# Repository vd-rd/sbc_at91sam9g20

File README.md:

# Microchip AT91SAM9G20

## Description
 The follow-up to my previous [SBC based on AT91SAM9260](https://github.com/vd-rd/sbc_at91sam9260), enhancing the board specs in computing power and flexibility. The board is smaller 60x40mm now (SAM9260 was 80x40mm) while keeping the same amount of supported RAM and interfaces. AT91SAM9G20 boosts core speed to 400MHz and bus speed to 133MHz.
 
Board overview (draft):
[TBD]

### Features

| Characteristic | Description |
| --- | --- |
| Dimensions | 60mm x 40mm |
| Processor | AT91SAM9G20 - ARM926EJ @ 400MHz |
| Oscillators |  18.432MHz main clock, 32.768kHz RTC |
| RAM | SDRAM 128MB max (2x512Mbit modules) |
| Storage | microSD |
| USB | 1 microUSB client, 2 USB Host|
| Ethernet | RMII header |
| WiFi/BT | N/A |
| Supply | USB 5V, ACIN 5V |

Common interfaces such as I2C, SPI, UART and GPIO are exposed on the header.

### Building and flashing

Build U-Boot and Linux kernel + rootFS - TBD

Flash to SDCard - TBD

### Resources

You can find all necesary information to build or evaluate the module here:
   - [Fabrication files](https://github.com/vd-rd/sbc_alw_a13/releases)

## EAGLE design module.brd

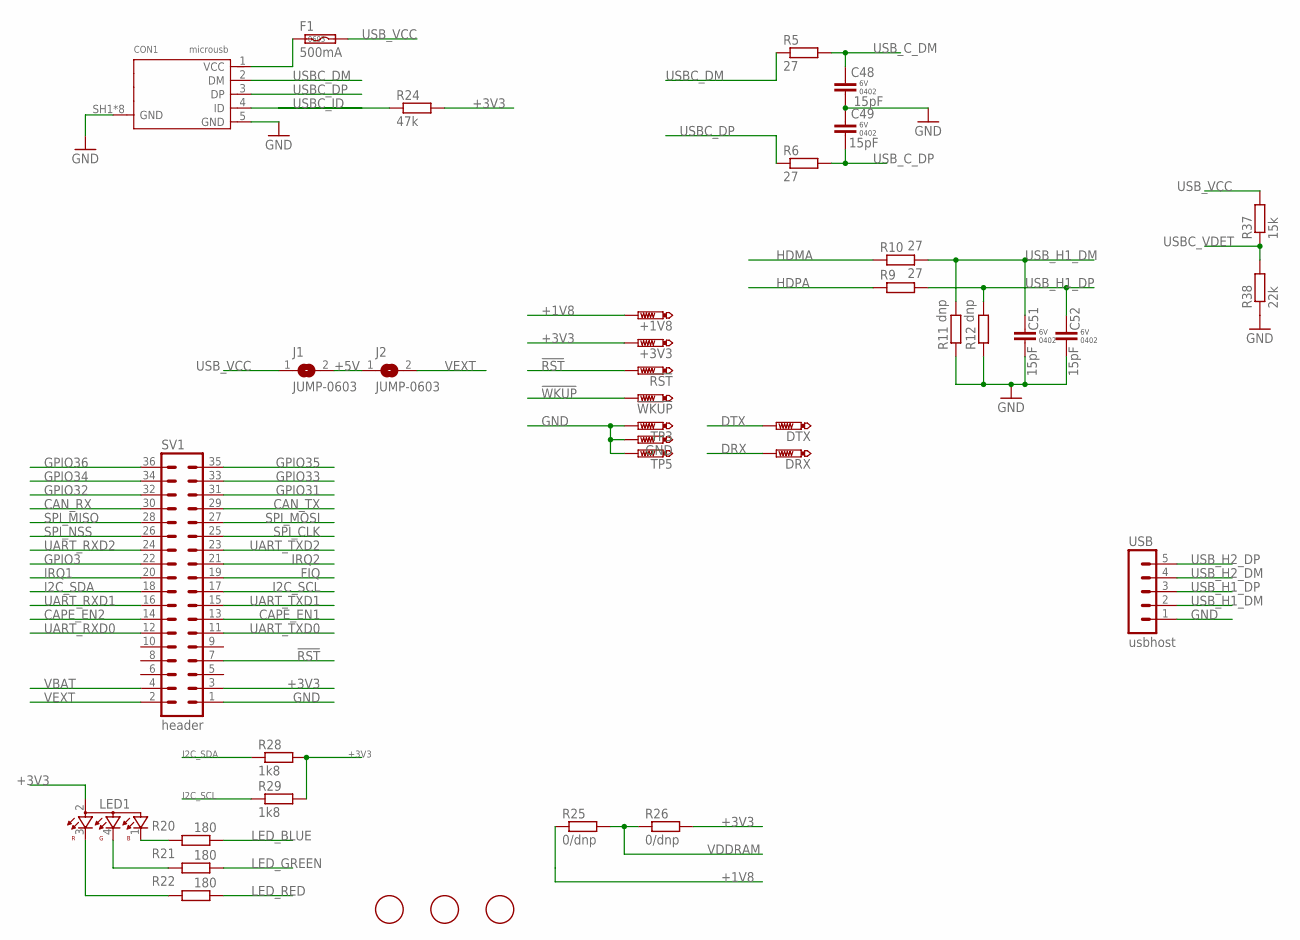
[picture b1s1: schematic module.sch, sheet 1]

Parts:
!RST: PTR1B1,27; B1,27
!WKUP: PTR1B1,27; B1,27
+1V8, +3V3: PTR1B1,27; B1,27
C48, C49, C51, C52: 15pF; C0402K
CON1: microusb; 10118194
DRX: PTR1B1,27; B1,27
DTX: PTR1B1,27; B1,27
F1: 500mA; F0603
GND: PTR1B1,27; B1,27
J1, J2: JUMP-0603; C0603
LED1: OSTB1204C1E; 321015RGB
R5, R6, R9, R10: 27; R0402
R11, R12: dnp; R0402
R20, R21, R22: 180; R0402
R24: 47k; R0402
R25, R26: 0/dnp; R0603
R28, R29: 1k8; R0402
R37: 15k; R0402
R38: 22k; R0402
SV1: header; MA18-2
TP3, TP5: PTR1B1,27; B1,27
U$1, U$2, U$3: FIDUCIAL; FIDUCIAL_1MM
USB: usbhost; MA05-1

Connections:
!RST: !RST.TP, SV1.7; also elsewhere on the board
!WKUP: !WKUP.TP; also elsewhere on the board
+1V8: +1V8.TP, R25.1; also elsewhere on the board
+3V3: +3V3.TP, LED1.2, R24.2, R26.2, R28.2, R29.2, SV1.3; also elsewhere on the board
+5V: J1.2, J2.1
CAN_RX: SV1.30
CAN_TX: SV1.29
CAPE_EN1: SV1.13; also elsewhere on the board
CAPE_EN2: SV1.14; also elsewhere on the board
DRX: DRX.TP; also elsewhere on the board
DTX: DTX.TP; also elsewhere on the board
FIQ: SV1.19; also elsewhere on the board
GND: C48.2, C49.2, C51.2, C52.2, CON1.5 (GND), CON1.SH1 (GND), CON1.SH2 (GND), CON1.SH3 (GND), CON1.SH4 (GND), CON1.SH5 (GND), CON1.SH6 (GND), CON1.SH7 (GND), CON1.SH8 (GND), GND.TP, R11.1, R12.1, R38.1, SV1.1, TP3.TP, TP5.TP, USB.1; also elsewhere on the board
GPIO3: SV1.22; also elsewhere on the board
GPIO31: SV1.31; also elsewhere on the board
GPIO32: SV1.32; also elsewhere on the board
GPIO33: SV1.33; also elsewhere on the board
GPIO34: SV1.34; also elsewhere on the board
GPIO35: SV1.35; also elsewhere on the board
GPIO36: SV1.36; also elsewhere on the board
HDMA: R10.1; also elsewhere on the board
HDPA: R9.1; also elsewhere on the board
I2C_SCL: R29.1, SV1.17; also elsewhere on the board
I2C_SDA: R28.1, SV1.18; also elsewhere on the board
IRQ1: SV1.20; also elsewhere on the board
IRQ2: SV1.21; also elsewhere on the board
LED_BLUE: R20.1; also elsewhere on the board
LED_GREEN: R21.1; also elsewhere on the board
LED_RED: R22.1; also elsewhere on the board
unnamed: CON1.1 (VCC), F1.1
unnamed: LED1.1, R20.2
unnamed: LED1.4, R21.2
unnamed: LED1.3, R22.2
SPI_CLK: SV1.25; also elsewhere on the board
SPI_MISO: SV1.28; also elsewhere on the board
SPI_MOSI: SV1.27; also elsewhere on the board
SPI_NSS: SV1.26; also elsewhere on the board
UART_RXD0: SV1.12; also elsewhere on the board
UART_RXD1: SV1.16; also elsewhere on the board
UART_RXD2: SV1.24; also elsewhere on the board
UART_TXD0: SV1.11; also elsewhere on the board
UART_TXD1: SV1.15; also elsewhere on the board
UART_TXD2: SV1.23; also elsewhere on the board
USBC_DM: CON1.2 (DM), R5.1
USBC_DP: CON1.3 (DP), R6.1
USBC_ID: CON1.4 (ID), R24.1; also elsewhere on the board
USBC_VDET: R37.1, R38.2; also elsewhere on the board
USB_C_DM: C48.1, R5.2; also elsewhere on the board
USB_C_DP: C49.1, R6.2; also elsewhere on the board
USB_H1_DM: C51.1, R10.2, R11.2, USB.2
USB_H1_DP: C52.1, R9.2, R12.2, USB.3
USB_H2_DM: USB.4
USB_H2_DP: USB.5
USB_VCC: F1.2, J1.1, R37.2
VBAT: SV1.4
VDDRAM: R25.2, R26.1; also elsewhere on the board
VEXT: J2.2, SV1.2

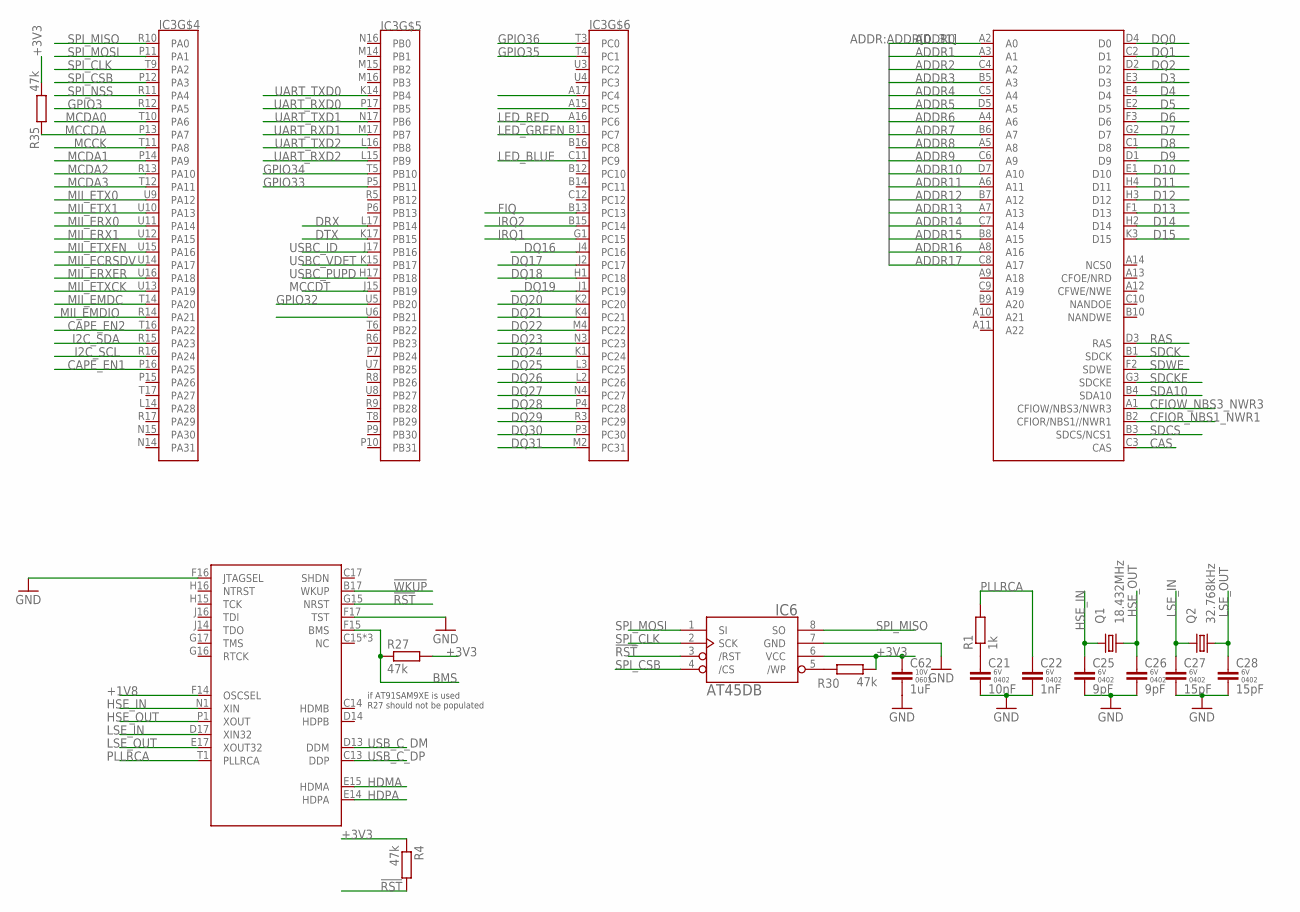
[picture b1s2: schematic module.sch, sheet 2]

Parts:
C21: 10nF; C0402K
C22: 1nF; C0402K
C25, C26: 9pF; C0402K
C27, C28: 15pF; C0402K
C62: 1uF; C0603
IC3: AT91SAM9260-BGA; BGA217C80P17X17_1500X1500X100
IC6: AT45DB-S; SO08-208
Q1: 18.432MHz; 3215
Q2: 32.768kHz; 3215
R1: 1k; R0402
R4, R27, R30, R35: 47k; R0402

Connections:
!RST: IC3.G15 (NRST), IC6.3 (/RST), R4.2; also elsewhere on the board
!WKUP: IC3.B17 (WKUP); also elsewhere on the board
+1V8: IC3.F14 (OSCSEL); also elsewhere on the board
+3V3: C62.1, IC6.6 (VCC), R4.1, R27.2, R30.2, R35.2; also elsewhere on the board
ADDR0: IC3.A2 (A0)
ADDR1: IC3.A3 (A1)
ADDR2: IC3.C4 (A2)
ADDR3: IC3.B5 (A3)
ADDR4: IC3.C5 (A4)
ADDR5: IC3.D5 (A5)
ADDR6: IC3.A4 (A6)
ADDR7: IC3.B6 (A7)
ADDR8: IC3.A5 (A8)
ADDR9: IC3.C6 (A9)
ADDR10: IC3.D7 (A10)
ADDR11: IC3.A6 (A11)
ADDR12: IC3.B7 (A12)
ADDR13: IC3.A7 (A13)
ADDR14: IC3.C7 (A14)
ADDR15: IC3.B8 (A15)
ADDR16: IC3.A8 (A16)
ADDR17: IC3.C8 (A17)
BMS: IC3.F15 (BMS), R27.1
CAPE_EN1: IC3.P16 (PA25); also elsewhere on the board
CAPE_EN2: IC3.T16 (PA22); also elsewhere on the board
CAS: IC3.C3 (CAS); also elsewhere on the board
CFIOR_NBS1_NWR1: IC3.B2 (CFIOR/NBS1//NWR1); also elsewhere on the board
CFIOW_NBS3_NWR3: IC3.A1 (CFIOW/NBS3/NWR3); also elsewhere on the board
D3: IC3.E3 (D3); also elsewhere on the board
D4: IC3.E4 (D4); also elsewhere on the board
D5: IC3.E2 (D5); also elsewhere on the board
D6: IC3.F3 (D6); also elsewhere on the board
D7: IC3.G2 (D7); also elsewhere on the board
D8: IC3.C1 (D8); also elsewhere on the board
D9: IC3.D1 (D9); also elsewhere on the board
D10: IC3.E1 (D10); also elsewhere on the board
D11: IC3.H4 (D11); also elsewhere on the board
D12: IC3.H3 (D12); also elsewhere on the board
D13: IC3.F1 (D13); also elsewhere on the board
D14: IC3.H2 (D14); also elsewhere on the board
D15: IC3.K3 (D15); also elsewhere on the board
DQ0: IC3.D4 (D0); also elsewhere on the board
DQ1: IC3.C2 (D1); also elsewhere on the board
DQ2: IC3.D2; also elsewhere on the board
DQ16: IC3.J4 (PC16); also elsewhere on the board
DQ17: IC3.J2 (PC17); also elsewhere on the board
DQ18: IC3.H1 (PC18); also elsewhere on the board
DQ19: IC3.J1 (PC19); also elsewhere on the board
DQ20: IC3.K2 (PC20); also elsewhere on the board
DQ21: IC3.K4 (PC21); also elsewhere on the board
DQ22: IC3.M4 (PC22); also elsewhere on the board
DQ23: IC3.N3 (PC23); also elsewhere on the board
DQ24: IC3.K1 (PC24); also elsewhere on the board
DQ25: IC3.L3 (PC25); also elsewhere on the board
DQ26: IC3.L2 (PC26); also elsewhere on the board
DQ27: IC3.N4 (PC27); also elsewhere on the board
DQ28: IC3.P4 (PC28); also elsewhere on the board
DQ29: IC3.R3 (PC29); also elsewhere on the board
DQ30: IC3.P3 (PC30); also elsewhere on the board
DQ31: IC3.M2 (PC31); also elsewhere on the board
DRX: IC3.L17 (PB14); also elsewhere on the board
DTX: IC3.K17 (PB15); also elsewhere on the board
FIQ: IC3.B13 (PC13); also elsewhere on the board
GND: C21.2, C22.2, C25.2, C26.2, C27.2, C28.2, C62.2, IC3.F17 (TST), IC6.7 (GND); also elsewhere on the board
GPIO3: IC3.R12 (PA5); also elsewhere on the board
GPIO31: IC3.U6 (PB21); also elsewhere on the board
GPIO32: IC3.U5 (PB20); also elsewhere on the board
GPIO33: IC3.P5 (PB11); also elsewhere on the board
GPIO34: IC3.T5 (PB10); also elsewhere on the board
GPIO35: IC3.T4 (PC1); also elsewhere on the board
GPIO36: IC3.T3 (PC0); also elsewhere on the board
HDMA: IC3.E15 (HDMA); also elsewhere on the board
HDPA: IC3.E14 (HDPA); also elsewhere on the board
HSE_IN: C25.1, IC3.N1 (XIN), Q1.1
HSE_OUT: C26.1, IC3.P1 (XOUT), Q1.3 (2)
I2C_SCL: IC3.R16 (PA24); also elsewhere on the board
I2C_SDA: IC3.R15 (PA23); also elsewhere on the board
IRQ1: IC3.G1 (PC15); also elsewhere on the board
IRQ2: IC3.B15 (PC14); also elsewhere on the board
LED_BLUE: IC3.C11 (PC9); also elsewhere on the board
LED_GREEN: IC3.B11 (PC7); also elsewhere on the board
LED_RED: IC3.A16 (PC6); also elsewhere on the board
LSE_IN: C27.1, IC3.D17 (XIN32), Q2.1
LSE_OUT: C28.1, IC3.E17 (XOUT32), Q2.2
MCCDA: IC3.P13 (PA7), R35.1; also elsewhere on the board
MCCDT: IC3.J15 (PB19); also elsewhere on the board
MCCK: IC3.T11 (PA8); also elsewhere on the board
MCDA0: IC3.T10 (PA6); also elsewhere on the board
MCDA1: IC3.P14 (PA9); also elsewhere on the board
MCDA2: IC3.R13 (PA10); also elsewhere on the board
MCDA3: IC3.T12 (PA11); also elsewhere on the board
MII_ECRSDV: IC3.U14 (PA17); also elsewhere on the board
MII_EMDC: IC3.T14 (PA20); also elsewhere on the board
MII_EMDIO: IC3.R14 (PA21); also elsewhere on the board
MII_ERX0: IC3.U11 (PA14); also elsewhere on the board
MII_ERX1: IC3.U12 (PA15); also elsewhere on the board
MII_ERXER: IC3.U16 (PA18); also elsewhere on the board
MII_ETX0: IC3.U9 (PA12); also elsewhere on the board
MII_ETX1: IC3.U10 (PA13); also elsewhere on the board
MII_ETXCK: IC3.U13 (PA19); also elsewhere on the board
MII_ETXEN: IC3.U15 (PA16); also elsewhere on the board
unnamed: C21.1, R1.1
unnamed: IC6.5 (/WP), R30.1
PLLRCA: C22.1, IC3.T1 (PLLRCA), R1.2
RAS: IC3.D3 (RAS); also elsewhere on the board
SDA10: IC3.B4 (SDA10); also elsewhere on the board
SDCK: IC3.B1 (SDCK); also elsewhere on the board
SDCKE: IC3.G3 (SDCKE); also elsewhere on the board
SDCS: IC3.B3 (SDCS/NCS1); also elsewhere on the board
SDWE: IC3.F2 (SDWE); also elsewhere on the board
SPI_CLK: IC3.T9 (PA2), IC6.2 (SCK); also elsewhere on the board
SPI_CSB: IC3.P12 (PA3), IC6.4 (/CS)
SPI_MISO: IC3.R10 (PA0), IC6.8 (SO); also elsewhere on the board
SPI_MOSI: IC3.P11 (PA1), IC6.1 (SI); also elsewhere on the board
SPI_NSS: IC3.R11 (PA4); also elsewhere on the board
UART_RXD0: IC3.P17 (PB5); also elsewhere on the board
UART_RXD1: IC3.M17 (PB7); also elsewhere on the board
UART_RXD2: IC3.L15 (PB9); also elsewhere on the board
UART_TXD0: IC3.K14 (PB4); also elsewhere on the board
UART_TXD1: IC3.N17 (PB6); also elsewhere on the board
UART_TXD2: IC3.L16 (PB8); also elsewhere on the board
USBC_ID: IC3.J17 (PB16); also elsewhere on the board
USBC_PUPD: IC3.H17 (PB18)
USBC_VDET: IC3.K15 (PB17); also elsewhere on the board
USB_C_DM: IC3.D13 (DDM); also elsewhere on the board
USB_C_DP: IC3.C13 (DDP); also elsewhere on the board

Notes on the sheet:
if AT91SAM9XE is used R27 should not be populated

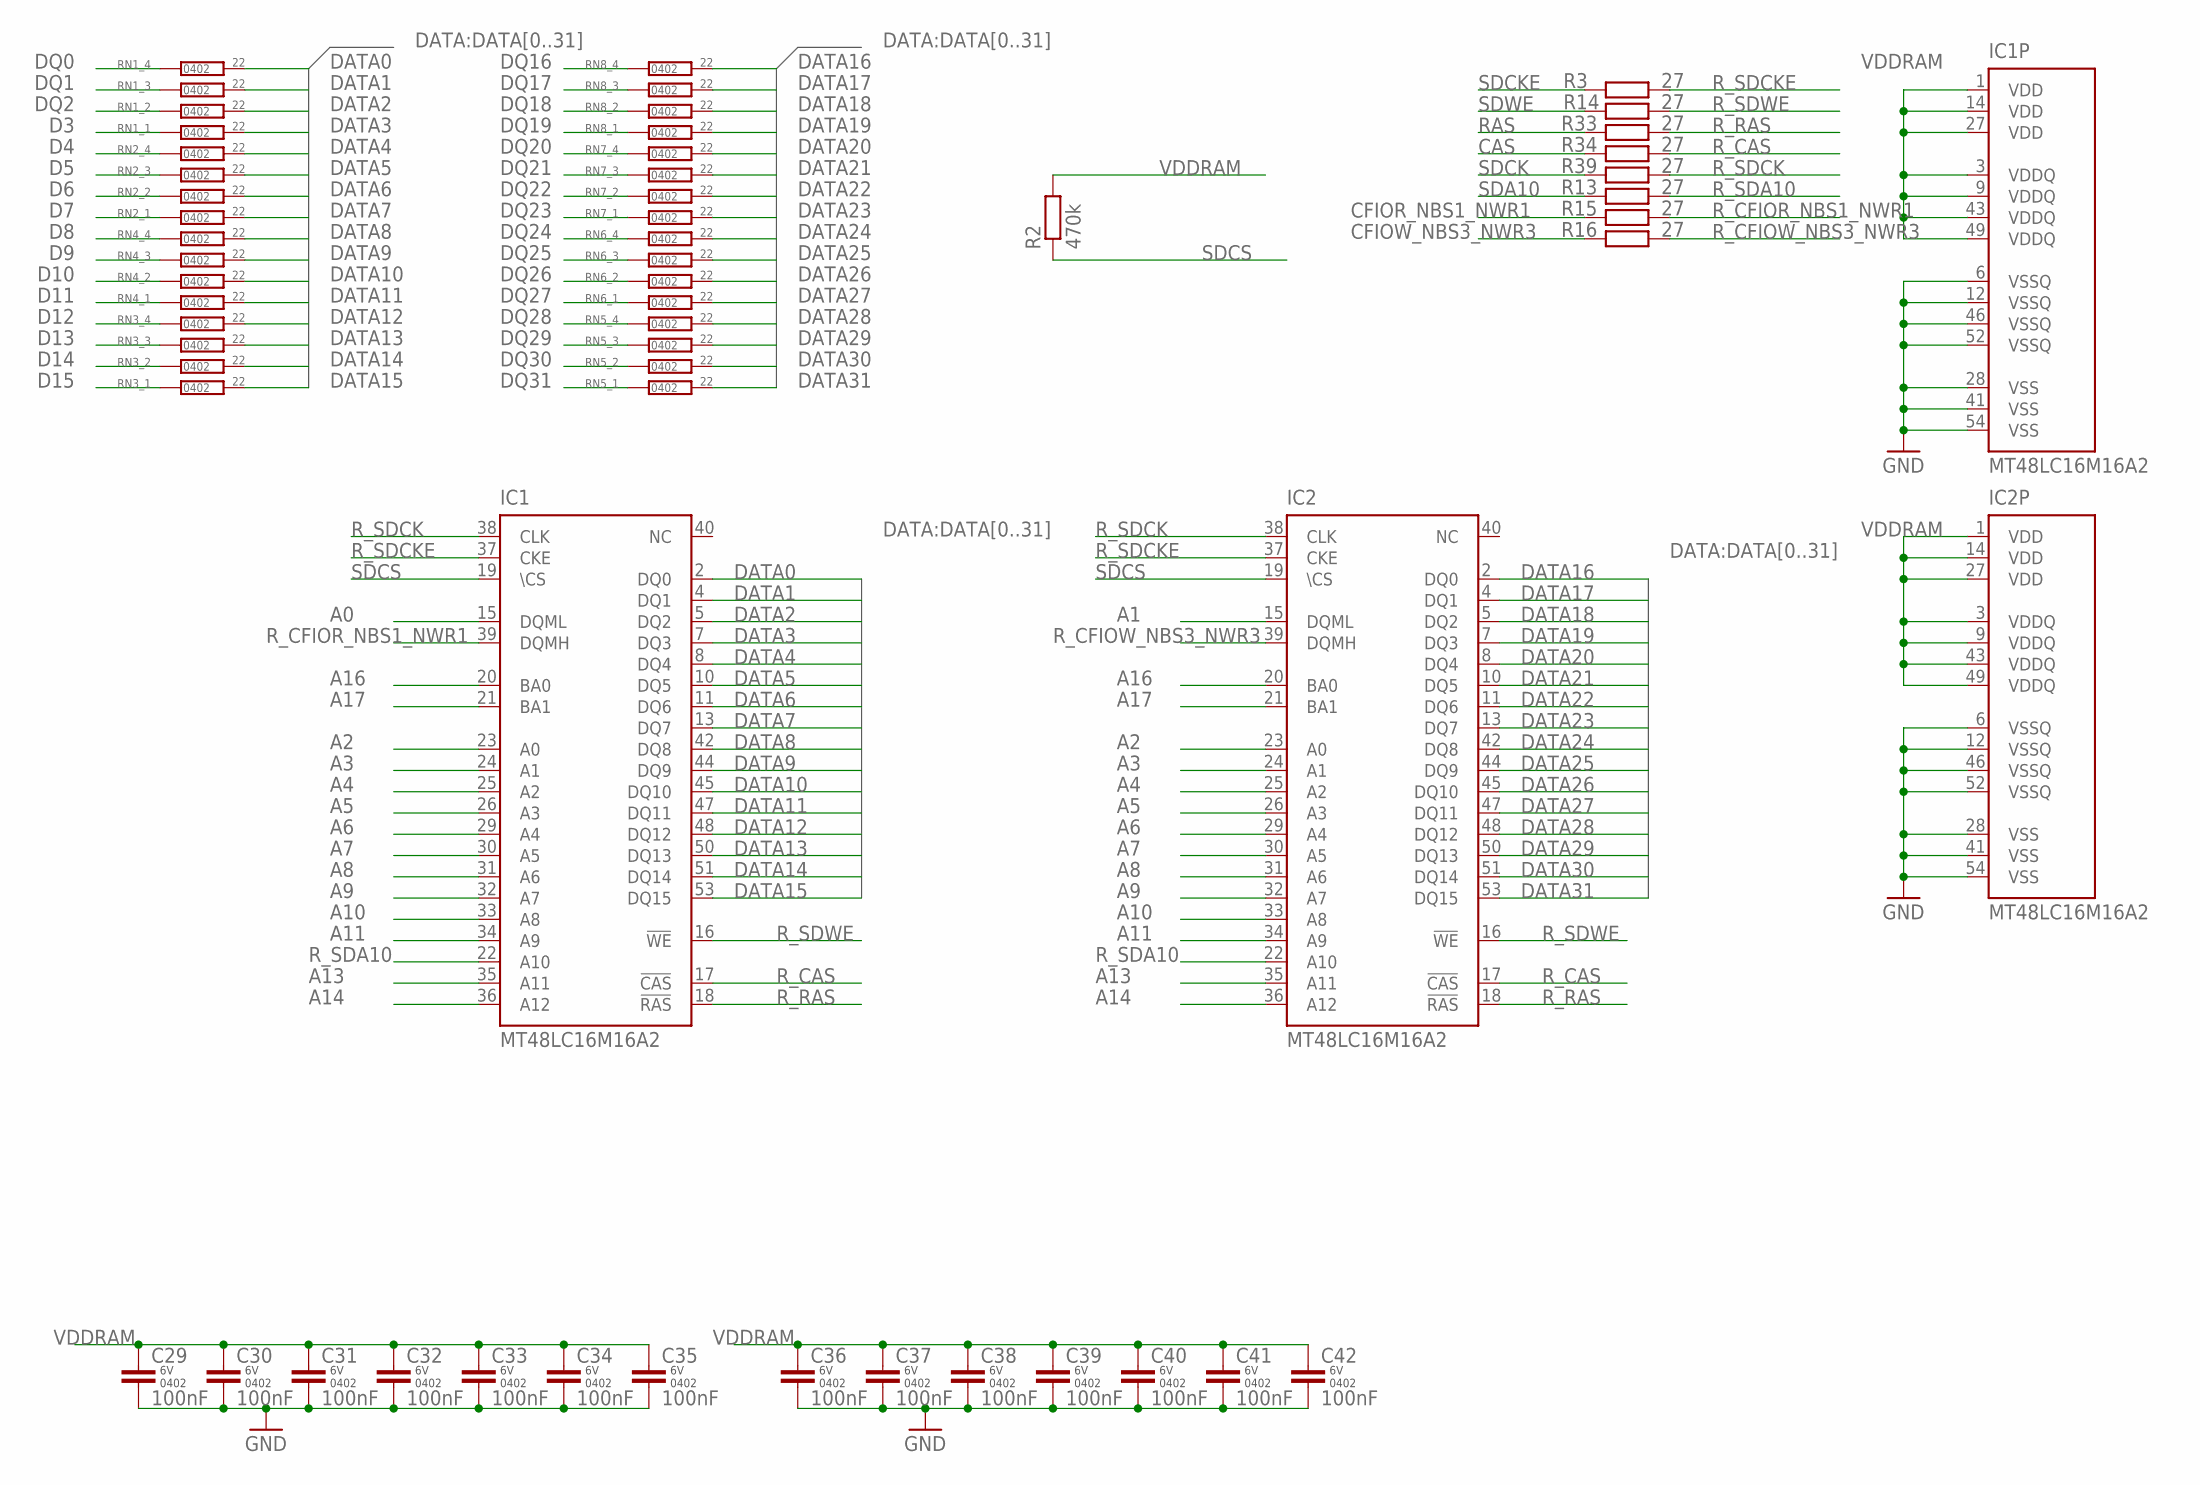
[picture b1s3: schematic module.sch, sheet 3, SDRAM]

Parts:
C29, C30, C31, C32, C33, C34, C35, C36, C37, C38, C39, C40, C41, C42: 100nF; C0402K
IC1, IC2: MT48LC16M16A2; TSOP54-400
R2: 470k; R0402
R3, R13, R14, R15, R16, R33, R34, R39: 27; R0402
RN1, RN2, RN3, RN4, RN5, RN6, RN7, RN8: 22; 4D02

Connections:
A0: IC1.15 (DQML)
A1: IC2.15 (DQML)
A2: IC1.23 (A0), IC2.23 (A0)
A3: IC1.24 (A1), IC2.24 (A1)
A4: IC1.25 (A2), IC2.25 (A2)
A5: IC1.26 (A3), IC2.26 (A3)
A6: IC1.29 (A4), IC2.29 (A4)
A7: IC1.30 (A5), IC2.30 (A5)
A8: IC1.31 (A6), IC2.31 (A6)
A9: IC1.32 (A7), IC2.32 (A7)
A10: IC1.33 (A8), IC2.33 (A8)
A11: IC1.34 (A9), IC2.34 (A9)
A13: IC1.35 (A11), IC2.35 (A11)
A14: IC1.36 (A12), IC2.36 (A12)
A16: IC1.20 (BA0), IC2.20 (BA0)
A17: IC1.21 (BA1), IC2.21 (BA1)
CAS: R34.1; also elsewhere on the board
CFIOR_NBS1_NWR1: R15.1; also elsewhere on the board
CFIOW_NBS3_NWR3: R16.1; also elsewhere on the board
D3: RN1.1; also elsewhere on the board
D4: RN2.4 (1); also elsewhere on the board
D5: RN2.3 (1); also elsewhere on the board
D6: RN2.2 (1); also elsewhere on the board
D7: RN2.1; also elsewhere on the board
D8: RN4.4 (1); also elsewhere on the board
D9: RN4.3 (1); also elsewhere on the board
D10: RN4.2 (1); also elsewhere on the board
D11: RN4.1; also elsewhere on the board
D12: RN3.4 (1); also elsewhere on the board
D13: RN3.3 (1); also elsewhere on the board
D14: RN3.2 (1); also elsewhere on the board
D15: RN3.1; also elsewhere on the board
DATA0: IC1.2 (DQ0), RN1.5 (2)
DATA1: IC1.4 (DQ1), RN1.6 (2)
DATA2: IC1.5 (DQ2), RN1.7 (2)
DATA3: IC1.7 (DQ3), RN1.8 (2)
DATA4: IC1.8 (DQ4), RN2.5 (2)
DATA5: IC1.10 (DQ5), RN2.6 (2)
DATA6: IC1.11 (DQ6), RN2.7 (2)
DATA7: IC1.13 (DQ7), RN2.8 (2)
DATA8: IC1.42 (DQ8), RN4.5 (2)
DATA9: IC1.44 (DQ9), RN4.6 (2)
DATA10: IC1.45 (DQ10), RN4.7 (2)
DATA11: IC1.47 (DQ11), RN4.8 (2)
DATA12: IC1.48 (DQ12), RN3.5 (2)
DATA13: IC1.50 (DQ13), RN3.6 (2)
DATA14: IC1.51 (DQ14), RN3.7 (2)
DATA15: IC1.53 (DQ15), RN3.8 (2)
DATA16: IC2.2 (DQ0), RN8.5 (2)
DATA17: IC2.4 (DQ1), RN8.6 (2)
DATA18: IC2.5 (DQ2), RN8.7 (2)
DATA19: IC2.7 (DQ3), RN8.8 (2)
DATA20: IC2.8 (DQ4), RN7.5 (2)
DATA21: IC2.10 (DQ5), RN7.6 (2)
DATA22: IC2.11 (DQ6), RN7.7 (2)
DATA23: IC2.13 (DQ7), RN7.8 (2)
DATA24: IC2.42 (DQ8), RN6.5 (2)
DATA25: IC2.44 (DQ9), RN6.6 (2)
DATA26: IC2.45 (DQ10), RN6.7 (2)
DATA27: IC2.47 (DQ11), RN6.8 (2)
DATA28: IC2.48 (DQ12), RN5.5 (2)
DATA29: IC2.50 (DQ13), RN5.6 (2)
DATA30: IC2.51 (DQ14), RN5.7 (2)
DATA31: IC2.53 (DQ15), RN5.8 (2)
DQ0: RN1.4 (1); also elsewhere on the board
DQ1: RN1.3 (1); also elsewhere on the board
DQ2: RN1.2 (1); also elsewhere on the board
DQ16: RN8.4 (1); also elsewhere on the board
DQ17: RN8.3 (1); also elsewhere on the board
DQ18: RN8.2 (1); also elsewhere on the board
DQ19: RN8.1; also elsewhere on the board
DQ20: RN7.4 (1); also elsewhere on the board
DQ21: RN7.3 (1); also elsewhere on the board
DQ22: RN7.2 (1); also elsewhere on the board
DQ23: RN7.1; also elsewhere on the board
DQ24: RN6.4 (1); also elsewhere on the board
DQ25: RN6.3 (1); also elsewhere on the board
DQ26: RN6.2 (1); also elsewhere on the board
DQ27: RN6.1; also elsewhere on the board
DQ28: RN5.4 (1); also elsewhere on the board
DQ29: RN5.3 (1); also elsewhere on the board
DQ30: RN5.2 (1); also elsewhere on the board
DQ31: RN5.1; also elsewhere on the board
GND: C29.2, C30.2, C31.2, C32.2, C33.2, C34.2, C35.2, C36.2, C37.2, C38.2, C39.2, C40.2, C41.2, C42.2, IC1.6 (VSSQ), IC1.12 (VSSQ), IC1.28 (VSS), IC1.41 (VSS), IC1.46 (VSSQ), IC1.52 (VSSQ), IC1.54 (VSS), IC2.6 (VSSQ), IC2.12 (VSSQ), IC2.28 (VSS), IC2.41 (VSS), IC2.46 (VSSQ), IC2.52 (VSSQ), IC2.54 (VSS); also elsewhere on the board
RAS: R33.1; also elsewhere on the board
R_CAS: IC1.17 (!CAS), IC2.17 (!CAS), R34.2
R_CFIOR_NBS1_NWR1: IC1.39 (DQMH), R15.2
R_CFIOW_NBS3_NWR3: IC2.39 (DQMH), R16.2
R_RAS: IC1.18 (!RAS), IC2.18 (!RAS), R33.2
R_SDA10: IC1.22 (A10), IC2.22 (A10), R13.2
R_SDCK: IC1.38 (CLK), IC2.38 (CLK), R39.2
R_SDCKE: IC1.37 (CKE), IC2.37 (CKE), R3.2
R_SDWE: IC1.16 (!WE), IC2.16 (!WE), R14.2
SDA10: R13.1; also elsewhere on the board
SDCK: R39.1; also elsewhere on the board
SDCKE: R3.1; also elsewhere on the board
SDCS: IC1.19 (\CS), IC2.19 (\CS), R2.1; also elsewhere on the board
SDWE: R14.1; also elsewhere on the board
VDDRAM: C29.1, C30.1, C31.1, C32.1, C33.1, C34.1, C35.1, C36.1, C37.1, C38.1, C39.1, C40.1, C41.1, C42.1, IC1.1 (VDD), IC1.3 (VDDQ), IC1.9 (VDDQ), IC1.14 (VDD), IC1.27 (VDD), IC1.43 (VDDQ), IC1.49 (VDDQ), IC2.1 (VDD), IC2.3 (VDDQ), IC2.9 (VDDQ), IC2.14 (VDD), IC2.27 (VDD), IC2.43 (VDDQ), IC2.49 (VDDQ), R2.2; also elsewhere on the board

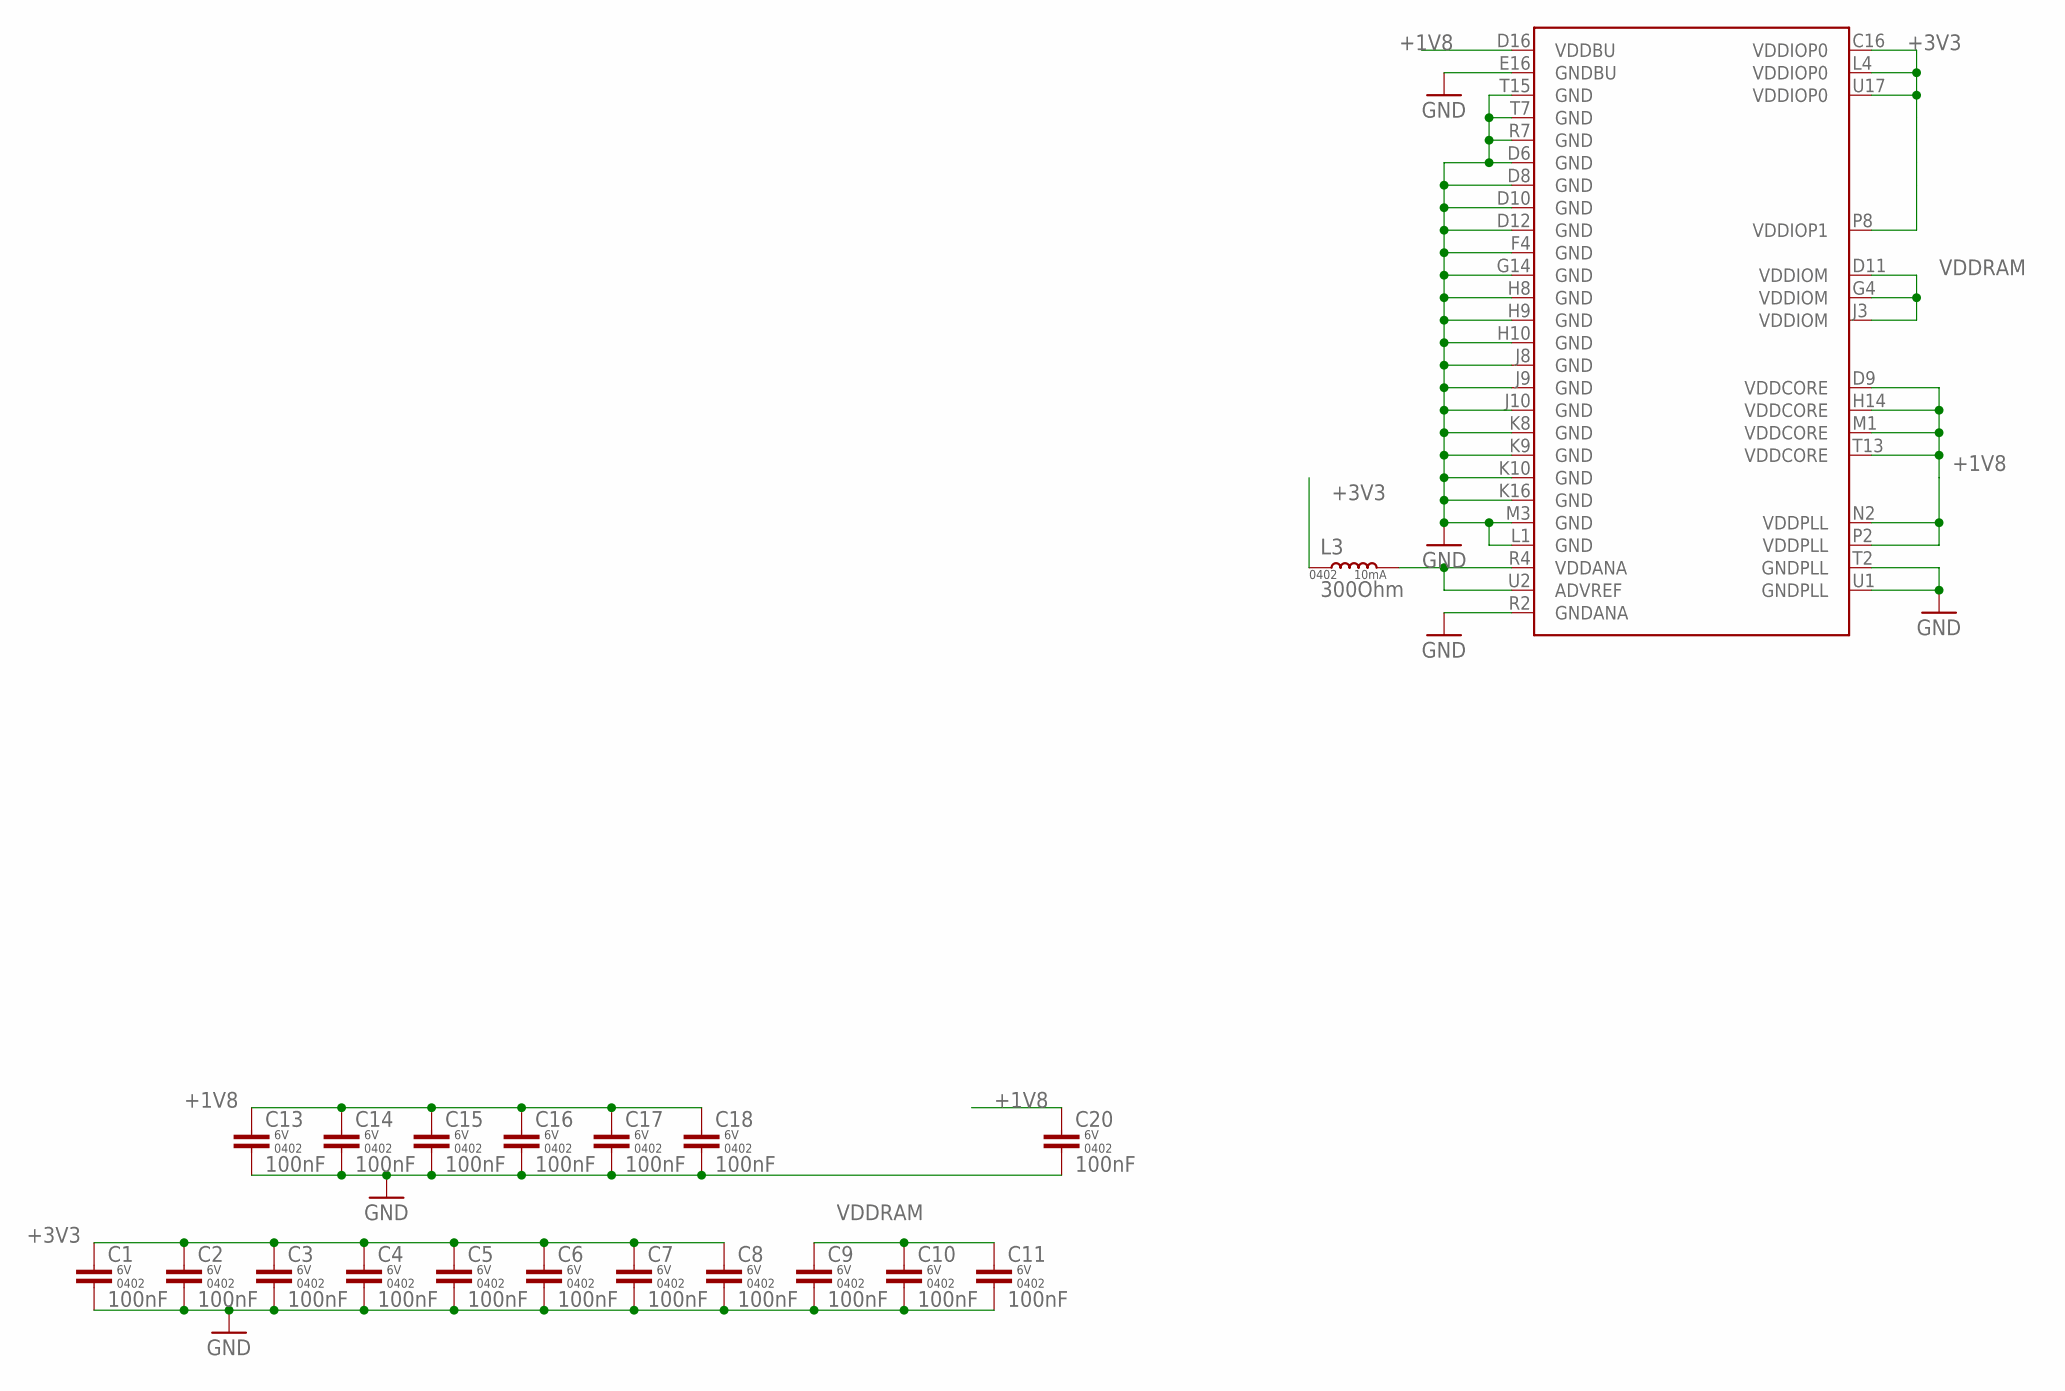
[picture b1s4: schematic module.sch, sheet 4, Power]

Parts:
C1, C2, C3, C4, C5, C6, C7, C8, C9, C10, C11, C13, C14, C15, C16, C17, C18, C20: 100nF; C0402K
IC3: AT91SAM9260-BGA; BGA217C80P17X17_1500X1500X100
L3: 300Ohm; L0402

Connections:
+1V8: C13.1, C14.1, C15.1, C16.1, C17.1, C18.1, C20.1, IC3.D9 (VDDCORE), IC3.D16 (VDDBU), IC3.H14 (VDDCORE), IC3.M1 (VDDCORE), IC3.N2 (VDDPLL), IC3.P2 (VDDPLL), IC3.T13 (VDDCORE); also elsewhere on the board
+3V3: C1.1, C2.1, C3.1, C4.1, C5.1, C6.1, C7.1, C8.1, IC3.C16 (VDDIOP0), IC3.L4 (VDDIOP0), IC3.P8 (VDDIOP1), IC3.U17 (VDDIOP0), L3.1; also elsewhere on the board
GND: C1.2, C2.2, C3.2, C4.2, C5.2, C6.2, C7.2, C8.2, C9.2, C10.2, C11.2, C13.2, C14.2, C15.2, C16.2, C17.2, C18.2, C20.2, IC3.D6 (GND), IC3.D8 (GND), IC3.D10 (GND), IC3.D12 (GND), IC3.E16 (GNDBU), IC3.F4 (GND), IC3.G14 (GND), IC3.H8 (GND), IC3.H9 (GND), IC3.H10 (GND), IC3.J8 (GND), IC3.J9 (GND), IC3.J10 (GND), IC3.K8 (GND), IC3.K9 (GND), IC3.K10 (GND), IC3.K16 (GND), IC3.L1 (GND), IC3.M3 (GND), IC3.R2 (GNDANA), IC3.R7 (GND), IC3.T2 (GNDPLL), IC3.T7 (GND), IC3.T15 (GND), IC3.U1 (GNDPLL); also elsewhere on the board
unnamed: IC3.R4 (VDDANA), IC3.U2 (ADVREF), L3.2
VDDRAM: C9.1, C10.1, C11.1, IC3.D11 (VDDIOM), IC3.G4 (VDDIOM), IC3.J3 (VDDIOM); also elsewhere on the board

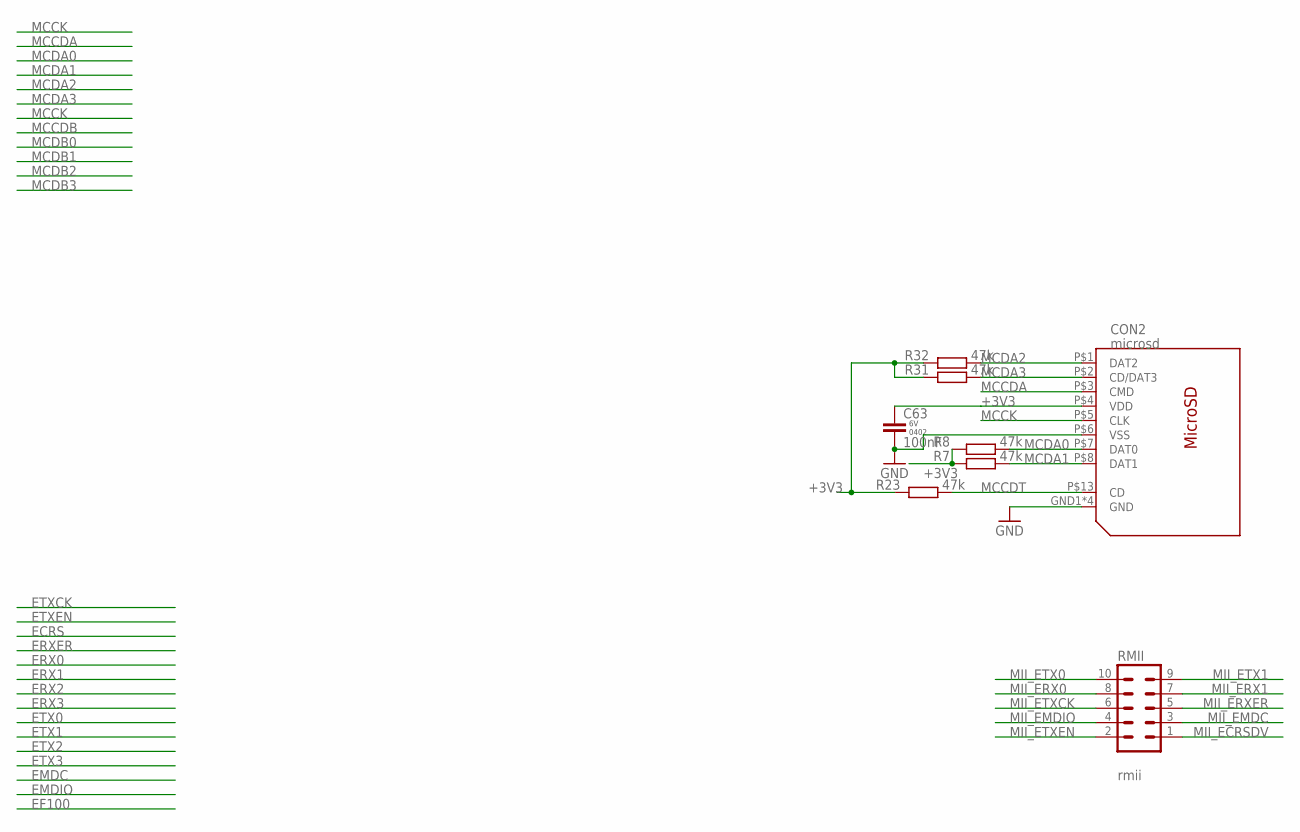
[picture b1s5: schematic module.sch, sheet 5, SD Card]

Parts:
C63: 100nF; C0402K
CON2: microsd; 112J
R7, R8, R23, R31, R32: 47k; R0402
RMII: rmii; MA05-2

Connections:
+3V3: C63.1, CON2.P$4 (VDD), R7.1, R8.1, R23.1, R31.1, R32.1; also elsewhere on the board
GND: C63.2, CON2.GND1 (GND), CON2.GND2 (GND), CON2.GND3 (GND), CON2.GND4 (GND), CON2.P$6 (VSS); also elsewhere on the board
MCCDA: CON2.P$3 (CMD); also elsewhere on the board
MCCDT: CON2.P$13 (CD), R23.2; also elsewhere on the board
MCCK: CON2.P$5 (CLK); also elsewhere on the board
MCDA0: CON2.P$7 (DAT0), R8.2; also elsewhere on the board
MCDA1: CON2.P$8 (DAT1), R7.2; also elsewhere on the board
MCDA2: CON2.P$1 (DAT2), R32.2; also elsewhere on the board
MCDA3: CON2.P$2 (CD/DAT3), R31.2; also elsewhere on the board
MII_ECRSDV: RMII.1; also elsewhere on the board
MII_EMDC: RMII.3; also elsewhere on the board
MII_EMDIO: RMII.4; also elsewhere on the board
MII_ERX0: RMII.8; also elsewhere on the board
MII_ERX1: RMII.7; also elsewhere on the board
MII_ERXER: RMII.5; also elsewhere on the board
MII_ETX0: RMII.10; also elsewhere on the board
MII_ETX1: RMII.9; also elsewhere on the board
MII_ETXCK: RMII.6; also elsewhere on the board
MII_ETXEN: RMII.2; also elsewhere on the board

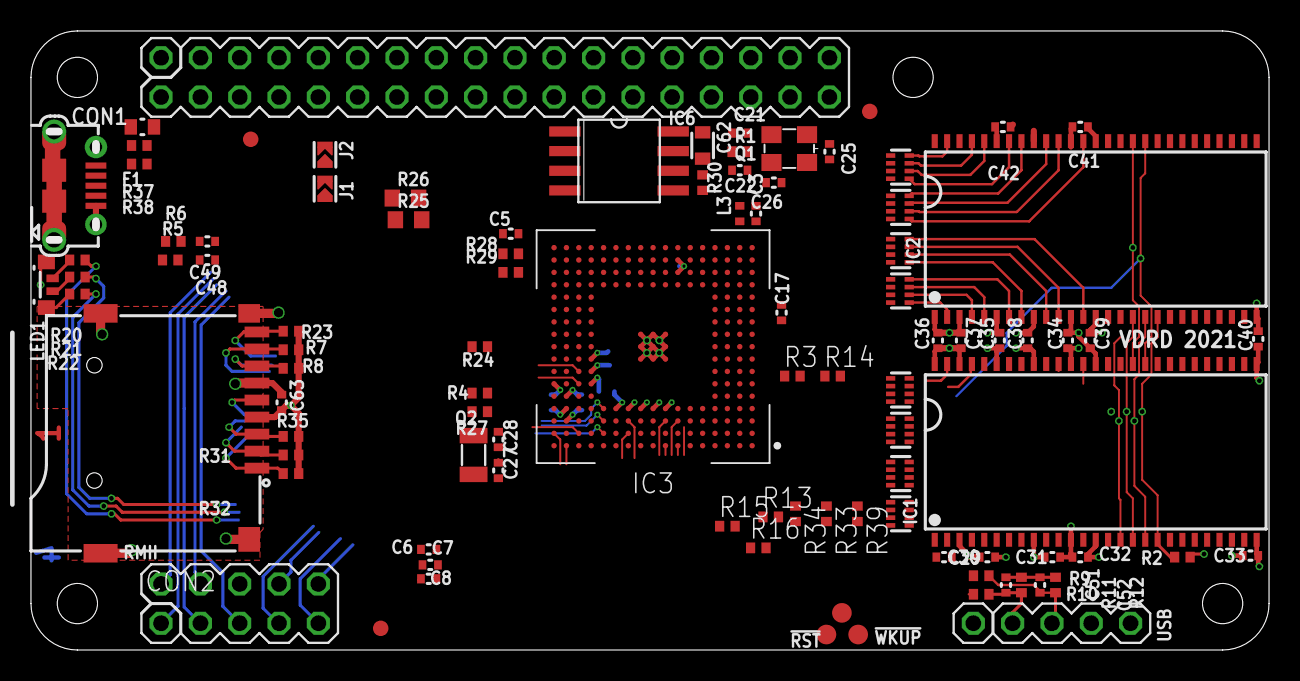
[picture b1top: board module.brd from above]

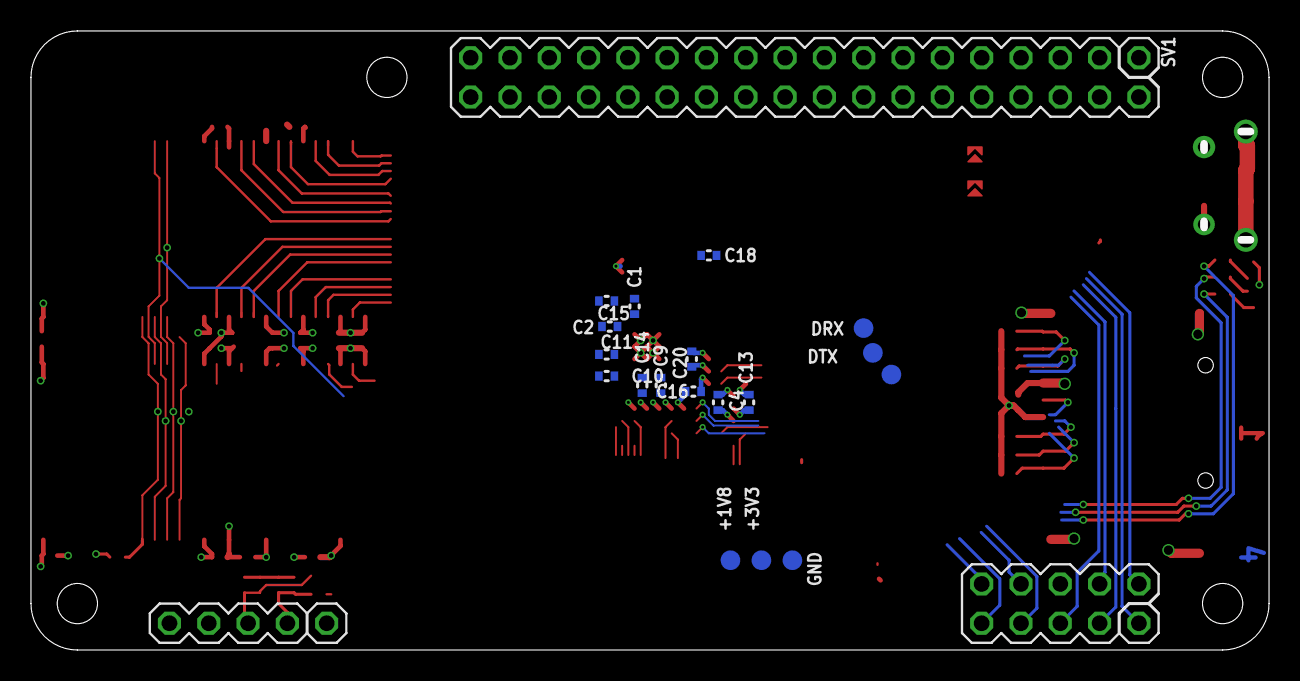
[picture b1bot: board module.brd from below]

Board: 4 copper layers, 80.0 x 40.0 mm, 115 parts (19 on the bottom side), 174 nets.

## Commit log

2019-05-10 project: structure bringup
2019-05-13 board: defined floorplan
2019-05-13 layout: added bga sdram variant
2021-02-24 design: sdram connections defined
2021-11-30 kicad bringup
2021-12-05 added decoupling caps
2021-12-07 define cpu nets
2021-12-08 small fixes
2021-12-13 more sdram routing
2022-01-03 add preliminary board render
2022-01-04 rearranged components
2022-01-13 added nor flash
2022-01-14 repositioned components on board, added nor storage
2022-01-16 add layer identification labels
2022-02-21 small ddr fixes
2022-03-09 fix usb connector
2022-03-24 fix project structure
2022-03-30 fix sdram wire width
2022-04-05 finish sdram
2022-04-05 small changes
2022-04-07 swap pmic for mcp16501
2022-04-07 upload new board preview
2022-04-07 add power rails
2022-04-07 add silk info
2022-04-15 fix spi bus
2022-05-03 add bga parts
2022-05-14 add usb esd
2022-05-15 more routing for rmii
2022-05-15 add nand flash
2022-05-22 fix eth header for compatibility
2022-05-28 route rmii bus
2022-05-28 define usb connector
2022-05-29 move bulk caps to input zone
2022-05-29 fixed wrong pullup on SDIO bus
2022-06-16 new routing work
2022-06-29 update project
2022-07-11 prepare for fab release
2022-11-22 update schematic on par with normal sdram
2024-05-13 bump format to kicad 8
2024-05-21 bump to kicad 8
2024-08-05 updated silkscreen labels
2024-08-05 remove extra files
2024-10-28 added tps and cleaned silk
2025-03-18 rework power delivery
2025-03-18 reorg project structure
2025-07-25 added rounded tracks
2026-01-26 backport changes from other boards
2026-01-26 updated board layout and project structure
2026-02-02 backport features
2026-02-03 modified pmic layout
2026-02-03 more routing
2026-04-30 almost done for rev 2
2026-05-02 updated gitignore
2026-05-23 small routing for v2
2026-05-23 cosmetics for rev2
2026-05-25 fix drc for rev2
